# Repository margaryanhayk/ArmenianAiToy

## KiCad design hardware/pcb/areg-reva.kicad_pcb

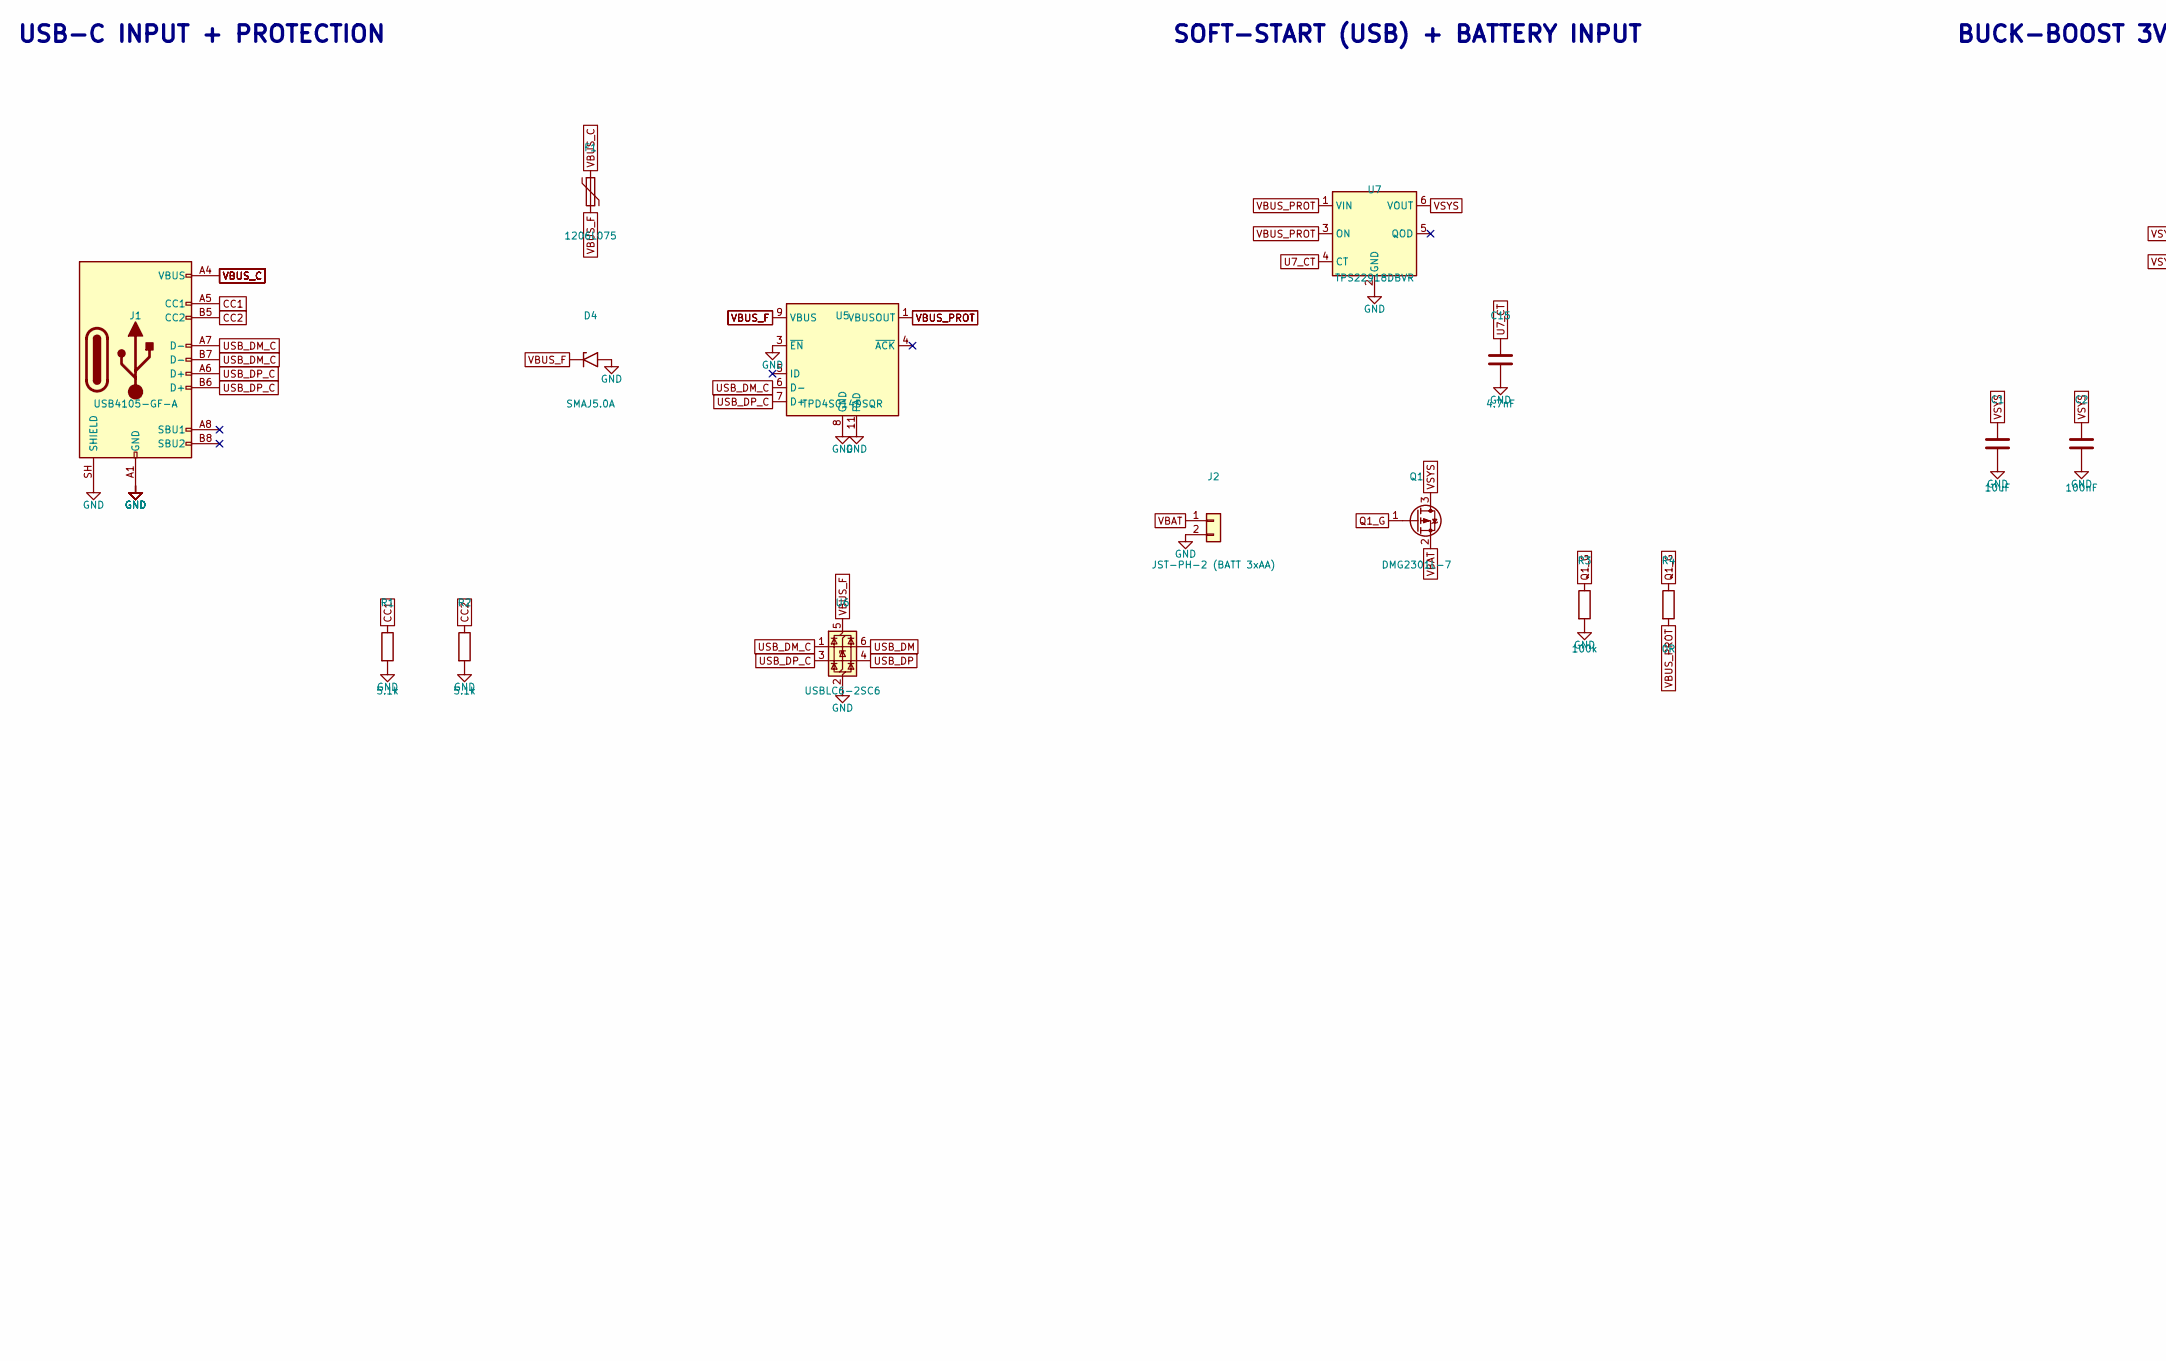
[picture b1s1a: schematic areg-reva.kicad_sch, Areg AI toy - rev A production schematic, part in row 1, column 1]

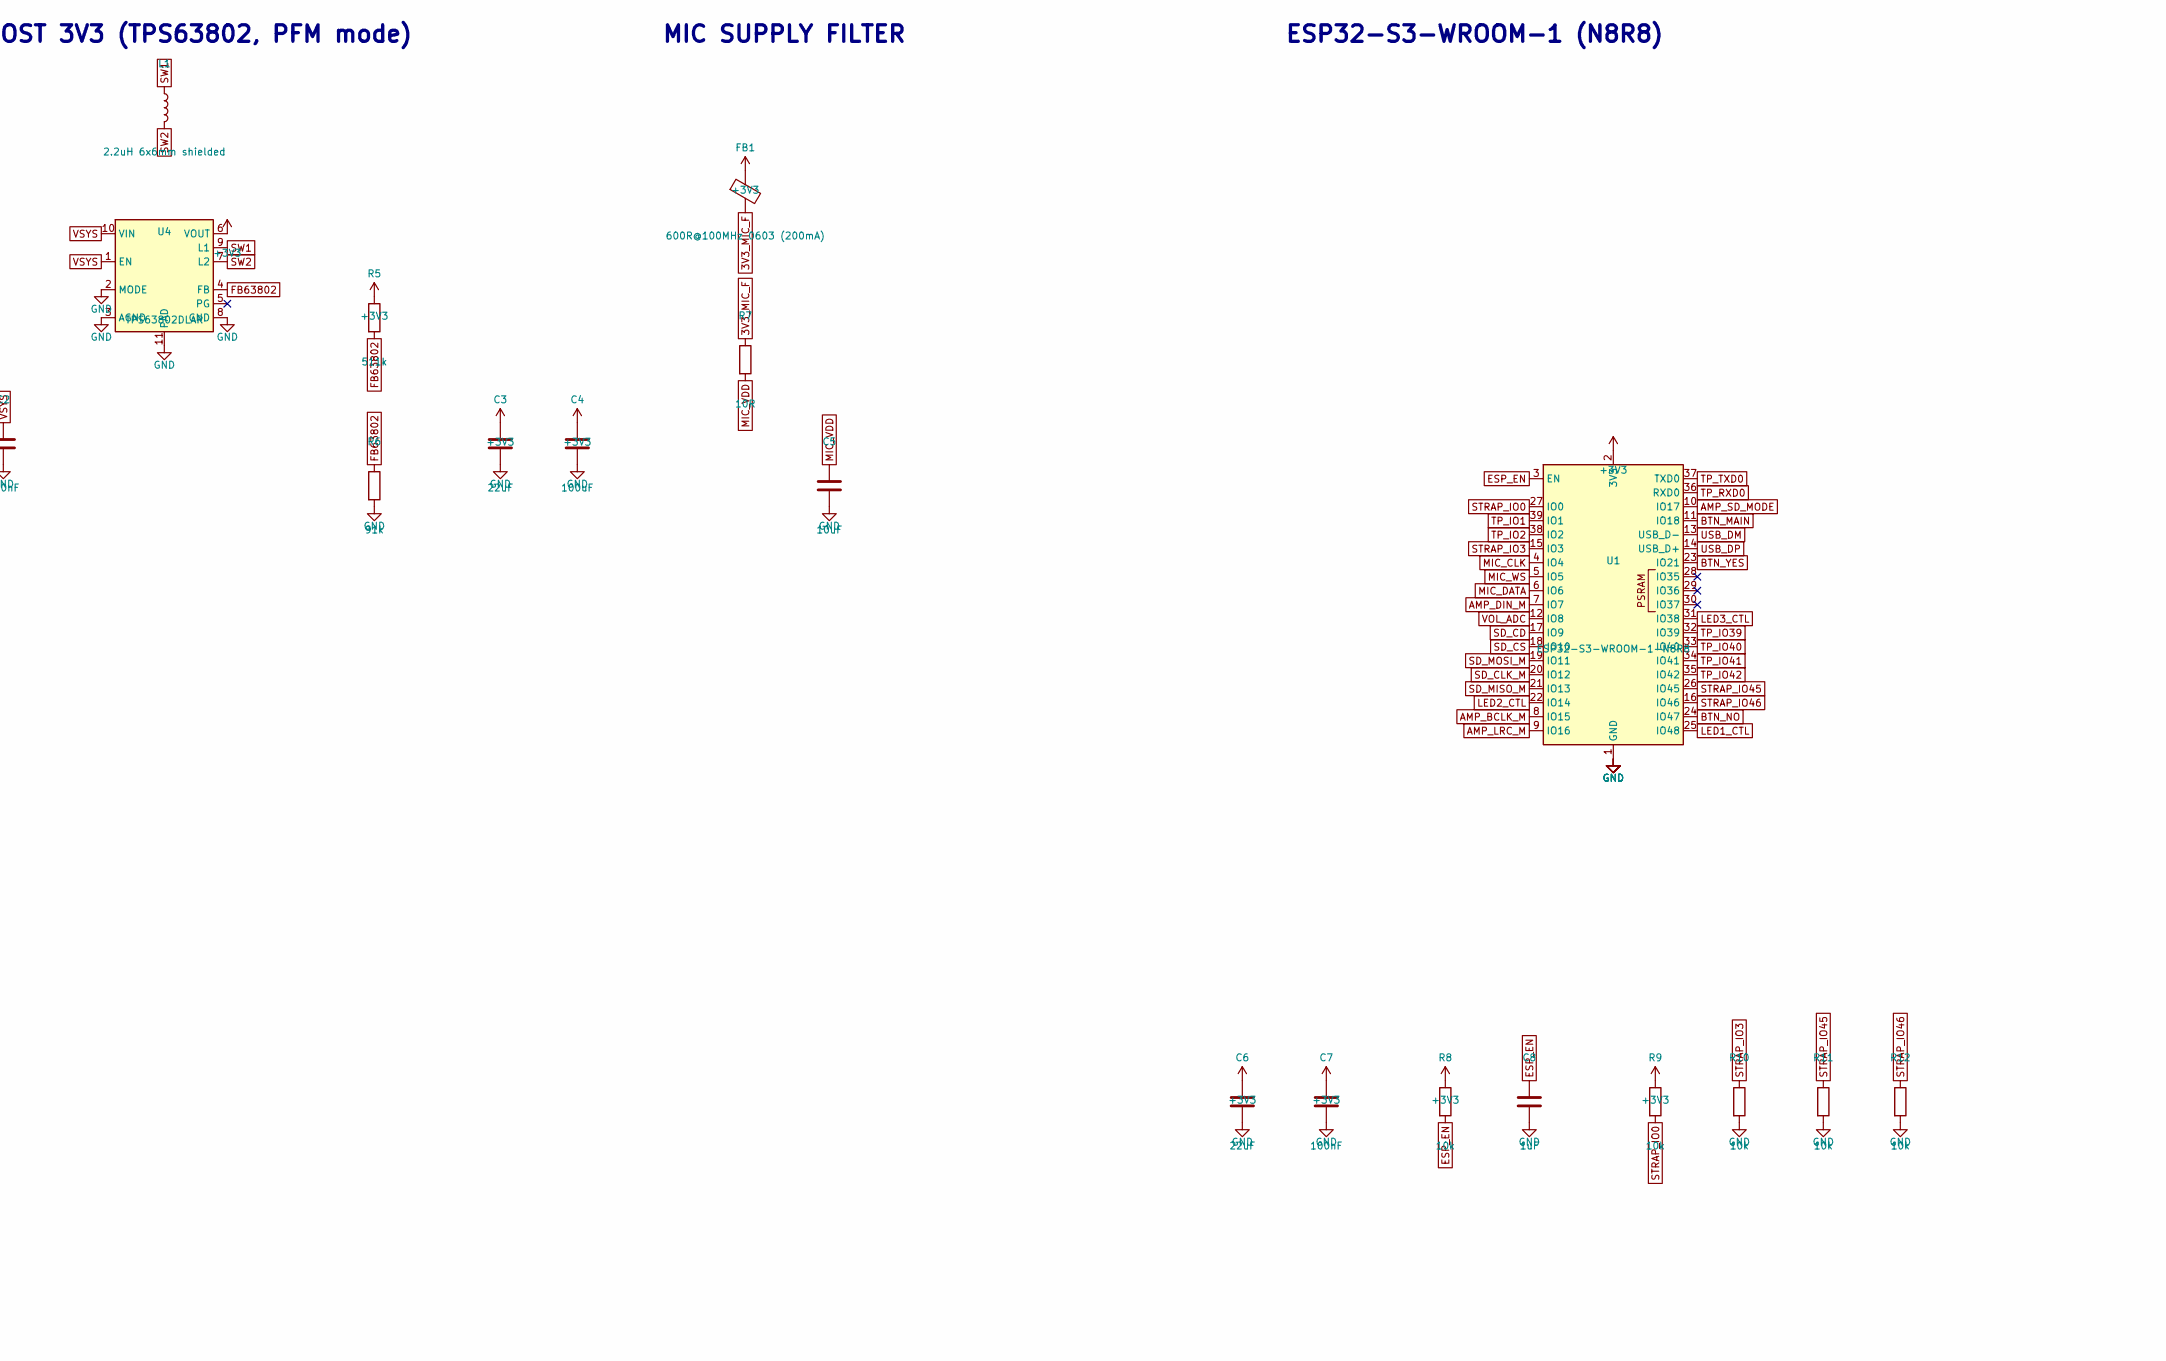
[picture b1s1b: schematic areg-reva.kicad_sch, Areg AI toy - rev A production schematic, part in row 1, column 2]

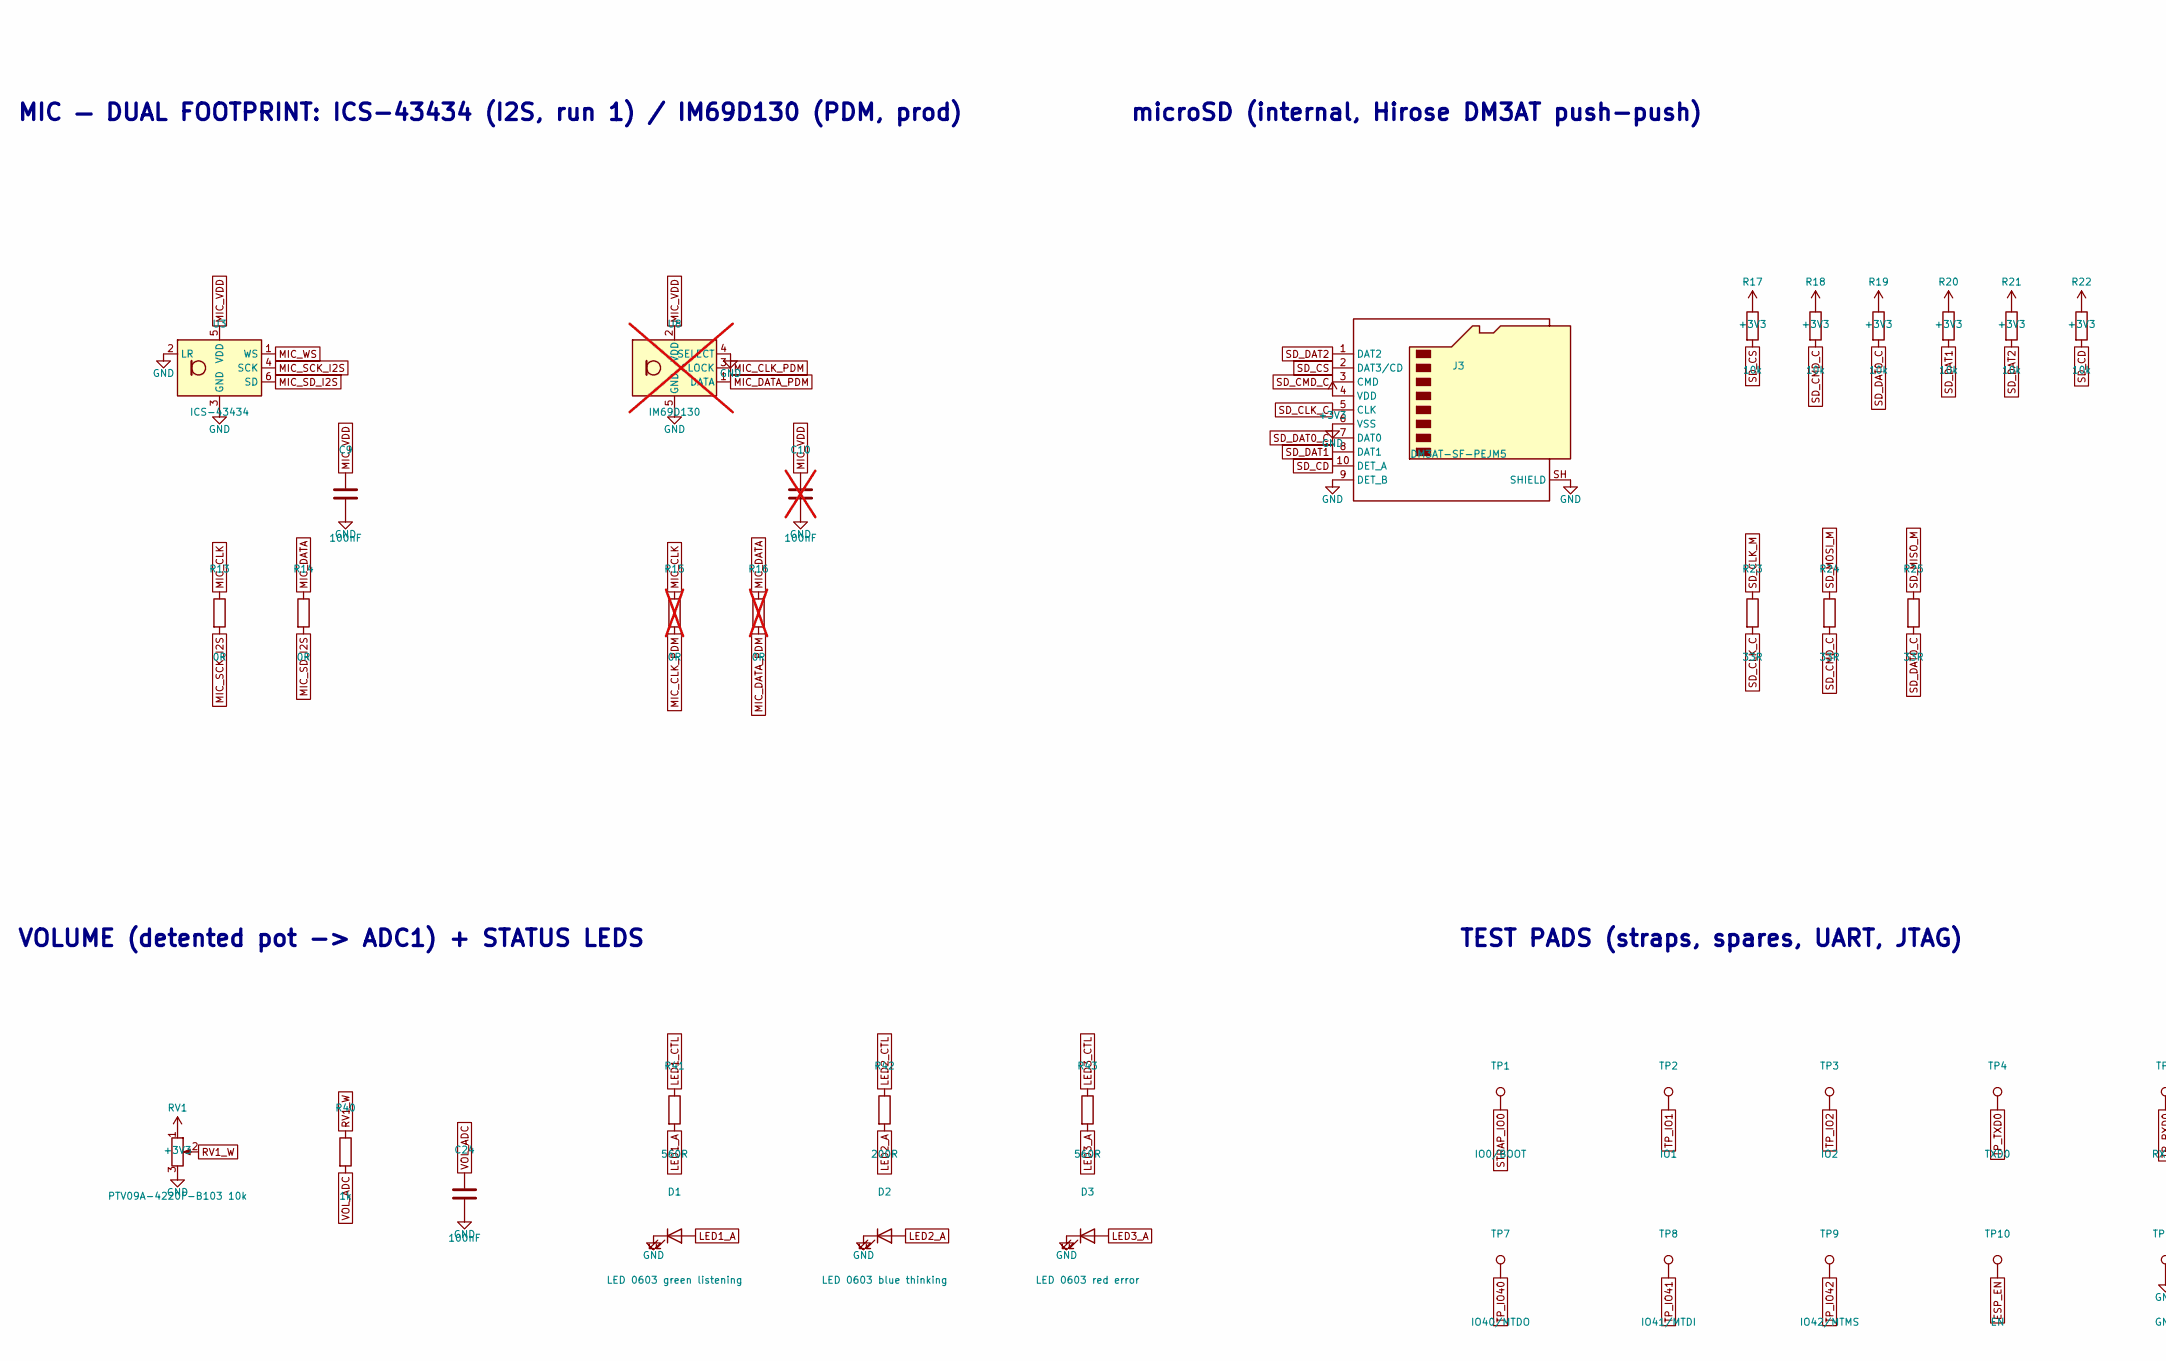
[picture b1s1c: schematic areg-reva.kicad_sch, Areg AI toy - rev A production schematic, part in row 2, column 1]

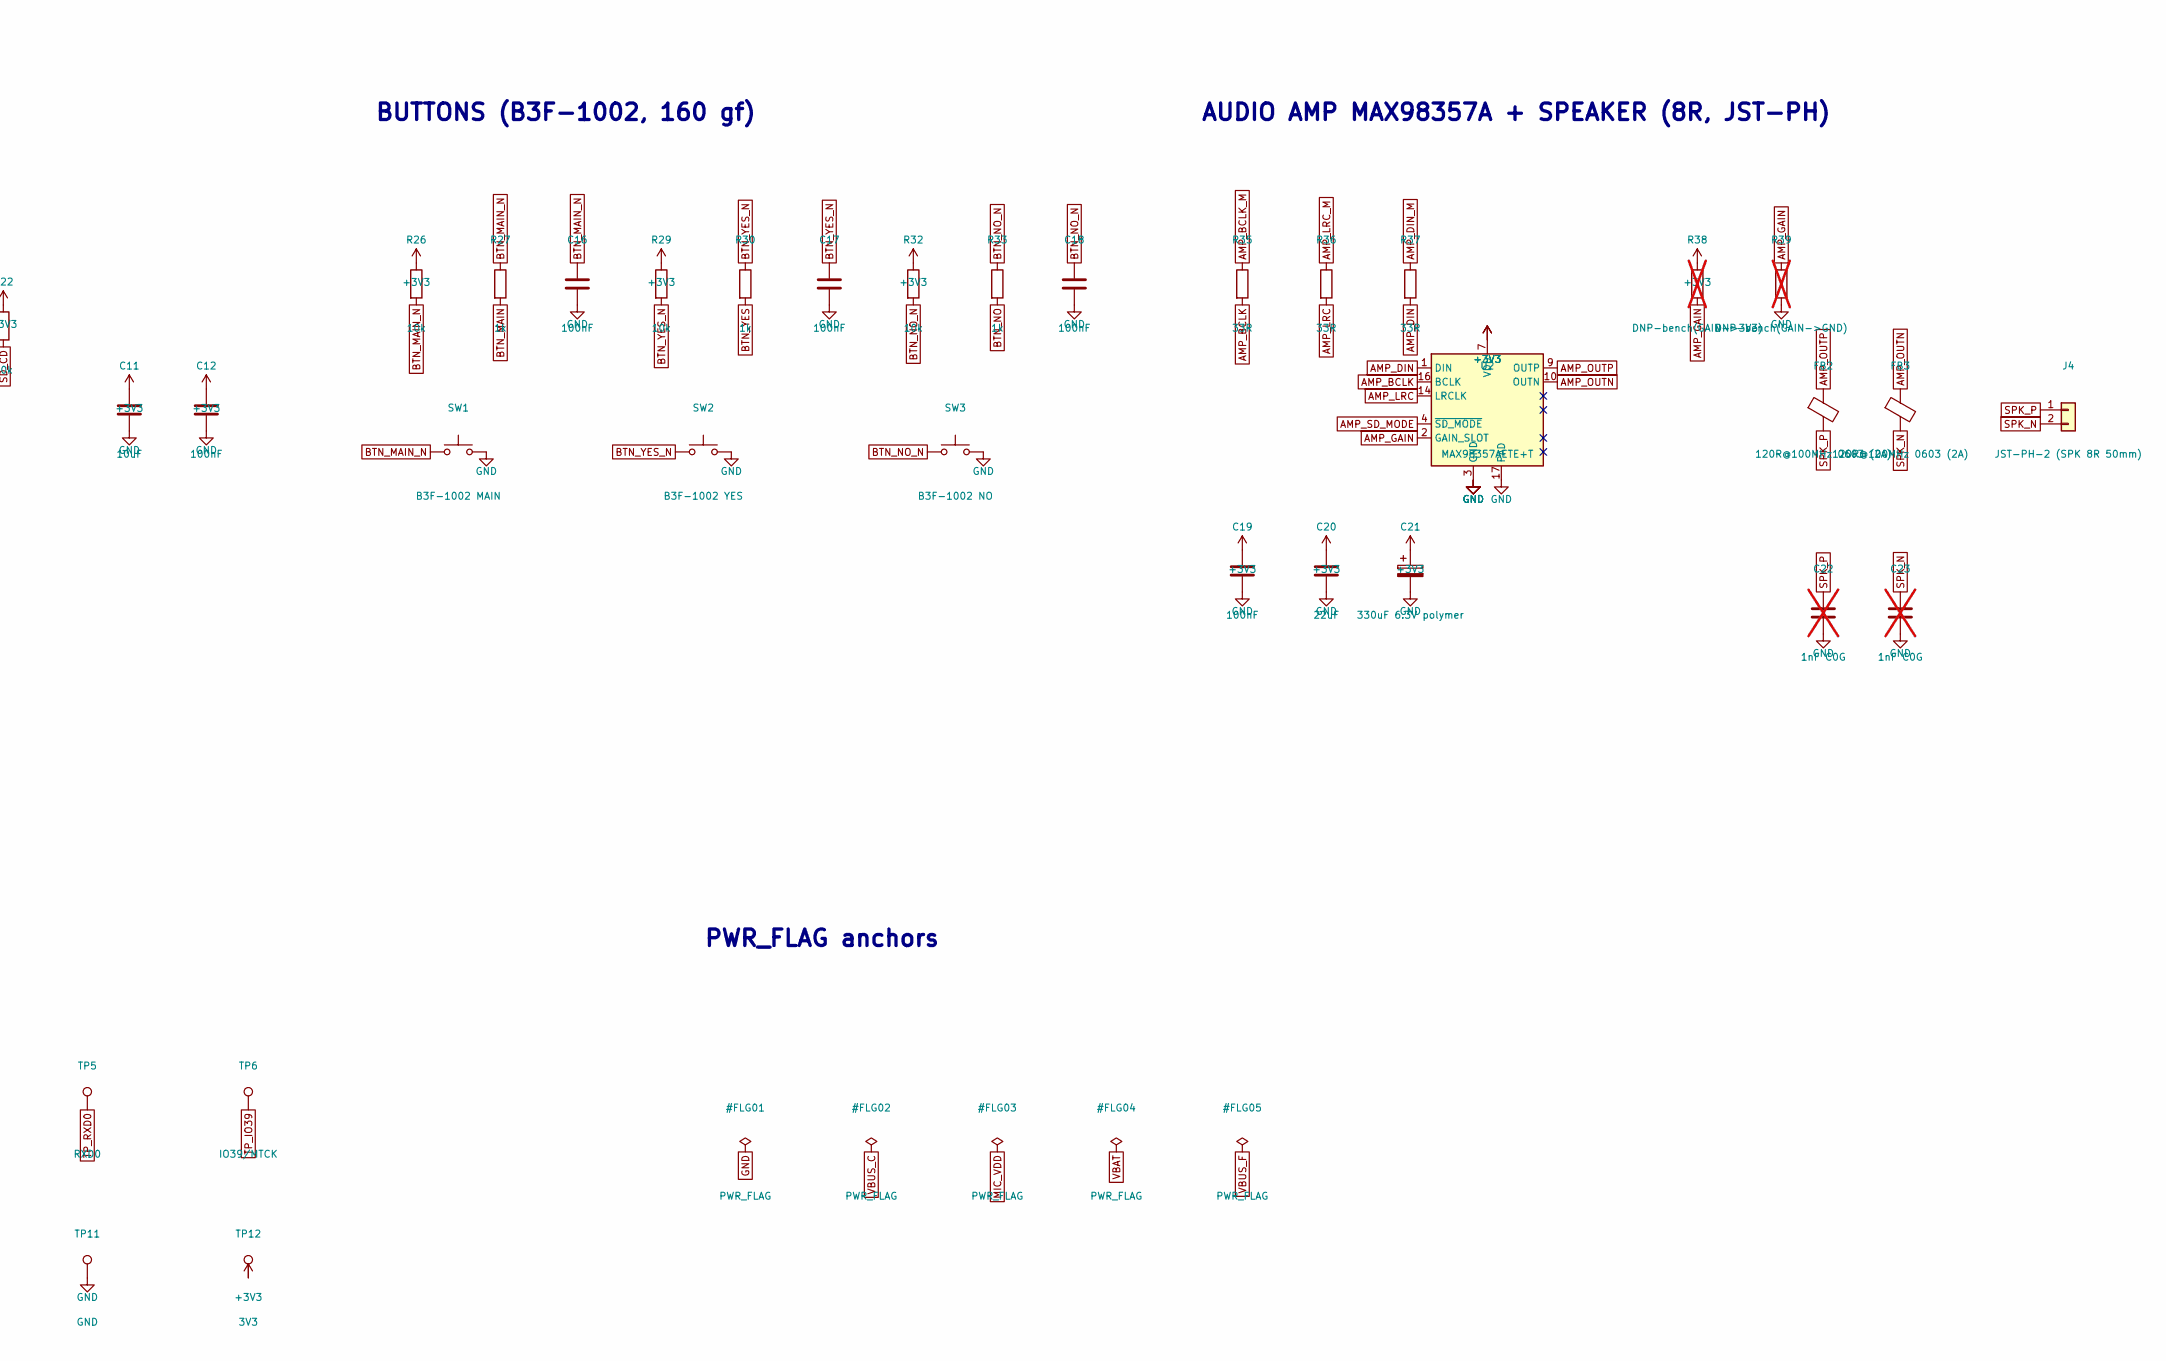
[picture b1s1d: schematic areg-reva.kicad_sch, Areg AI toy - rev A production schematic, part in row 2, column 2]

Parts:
C1, C5, C11: 10uF; C_0603_1608Metric; LCSC C19702
C2, C7, C9, C12, C16, C17, C18, C19, C24: 100nF; C_0402_1005Metric; LCSC C1525
C3, C6, C20: 22uF; C_0603_1608Metric
C4: 100uF; C_1206_3216Metric
C8: 1uF; C_0402_1005Metric; LCSC C52923
C10: 100nF; C_0402_1005Metric; LCSC C1525; not fitted
C15: 4.7nF; C_0402_1005Metric
C21: 330uF 6.3V polymer; CP_EIA-7343-31_Kemet-D; LCSC C79113
C22, C23: 1nF C0G; C_0402_1005Metric; not fitted
D1: LED 0603 green listening; LED_0603_1608Metric
D2: LED 0603 blue thinking; LED_0603_1608Metric
D3: LED 0603 red error; LED_0603_1608Metric
D4: SMAJ5.0A; D_SMA; LCSC C83329
F1: 1206L075; Fuse_1206_3216Metric
FB1: 600R@100MHz 0603 (200mA); L_0603_1608Metric; LCSC C1002
FB2, FB3: 120R@100MHz 0603 (2A); L_0603_1608Metric; LCSC C14709
J1: USB4105-GF-A; USB_C_Receptacle_GCT_USB4105-xx-A_16P_TopMnt_Horizontal
J2: JST-PH-2 (BATT 3xAA); JST_PH_B2B-PH-K_1x02_P2.00mm_Vertical
J3: DM3AT-SF-PEJM5; microSD_HC_Hirose_DM3AT-SF-PEJM5
J4: JST-PH-2 (SPK 8R 50mm); JST_PH_B2B-PH-K_1x02_P2.00mm_Vertical
L1: 2.2uH 6x6mm shielded; L_TDK_VLS6045EX_VLS6045AF; LCSC C2849533
Q1: DMG2301L-7; SOT-23; LCSC C102619
R1, R2: 5.1k; R_0402_1005Metric; LCSC C25905
R3: 100k; R_0402_1005Metric; LCSC C25741
R4, R13, R14: 0R; R_0603_1608Metric
R5: 511k; R_0603_1608Metric
R6: 91k; R_0603_1608Metric
R7: 10R; R_0402_1005Metric
R8, R9, R10, R11, R12, R17, R18, R19, R20, R21, R22, R26, R29, R32: 10k; R_0402_1005Metric; LCSC C25744
R15, R16: 0R; R_0603_1608Metric; not fitted
R23, R24, R25, R35, R36, R37: 33R; R_0603_1608Metric
R27, R30, R33, R40: 1k; R_0402_1005Metric; LCSC C11702
R38: DNP-bench(GAIN->3V3); R_0402_1005Metric; not fitted
R39: DNP-bench(GAIN->GND); R_0402_1005Metric; not fitted
R41, R43: 560R; R_0603_1608Metric
R42: 200R; R_0603_1608Metric
RV1: PTV09A-4220F-B103 10k; Potentiometer_Bourns_PTV09A-1_Single_Vertical
SW1: B3F-1002 MAIN; SW_TH_Tactile_Omron_B3F-100x
SW2: B3F-1002 YES; SW_TH_Tactile_Omron_B3F-100x
SW3: B3F-1002 NO; SW_TH_Tactile_Omron_B3F-100x
TP1: IO0/BOOT; TestPoint_Pad_1.5x1.5mm
TP2: IO1; TestPoint_Pad_1.5x1.5mm
TP3: IO2; TestPoint_Pad_1.5x1.5mm
TP4: TXD0; TestPoint_Pad_1.5x1.5mm
TP5: RXD0; TestPoint_Pad_1.5x1.5mm
TP6: IO39/MTCK; TestPoint_Pad_1.5x1.5mm
TP7: IO40/MTDO; TestPoint_Pad_1.5x1.5mm
TP8: IO41/MTDI; TestPoint_Pad_1.5x1.5mm
TP9: IO42/MTMS; TestPoint_Pad_1.5x1.5mm
TP10: EN; TestPoint_Pad_1.5x1.5mm
TP11: GND; TestPoint_Pad_1.5x1.5mm
TP12: 3V3; TestPoint_Pad_1.5x1.5mm
U1: ESP32-S3-WROOM-1-N8R8; ESP32-S3-WROOM-1
U2: MAX98357AETE+T; TQFN-16-1EP_3x3mm_P0.5mm_EP1.6x1.6mm; LCSC C910544
U3: ICS-43434; InvenSense_ICS-43434-6_3.5x2.65mm
U4: TPS63802DLAR; Texas_S-PVSON-N10
U5: TPD4S014DSQR; Texas_DSQ0010A_WSON-10-1EP_2x2mm_P0.4mm_EP0.9x1.5mm
U6: USBLC6-2SC6; SOT-23-6; LCSC C7519
U7: TPS22918DBVR; SOT-23-6; LCSC C131941
U8: IM69D130; Infineon_PG-LLGA-5-1; not fitted

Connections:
3V3_MIC_F: FB1.2, R7.1
+3V3: C3.1, C4.1, C6.1, C7.1, C11.1, C12.1, C19.1, C20.1, C21.1, FB1.1, J3.4 (VDD), R5.1, R8.1, R9.1, R17.1, R18.1, R19.1, R20.1, R21.1, R22.1, R26.1, R29.1, R32.1, R38.1, RV1.1, TP12.1, U1.2 (3V3), U2.7 (VDD), U2.8 (VDD), U4.6 (VOUT)
AMP_BCLK: R35.2, U2.16 (BCLK)
AMP_BCLK_M: R35.1, U1.8 (IO15)
AMP_DIN: R37.2, U2.1 (DIN)
AMP_DIN_M: R37.1, U1.7 (IO7)
AMP_GAIN: R38.2, R39.1, U2.2 (GAIN_SLOT)
AMP_LRC: R36.2, U2.14 (LRCLK)
AMP_LRC_M: R36.1, U1.9 (IO16)
AMP_OUTN: FB3.1, U2.10 (OUTN)
AMP_OUTP: FB2.1, U2.9 (OUTP)
AMP_SD_MODE: U1.10 (IO17), U2.4 (~SD_MODE)
BTN_MAIN: R27.2, U1.11 (IO18)
BTN_MAIN_N: C16.1, R26.2, R27.1, SW1.1
BTN_NO: R33.2, U1.24 (IO47)
BTN_NO_N: C18.1, R32.2, R33.1, SW3.1
BTN_YES: R30.2, U1.23 (IO21)
BTN_YES_N: C17.1, R29.2, R30.1, SW2.1
CC1: J1.A5 (CC1), R1.1
CC2: J1.B5 (CC2), R2.1
ESP_EN: C8.1, R8.2, TP10.1, U1.3 (EN)
FB63802: R5.2, R6.1, U4.4 (FB)
GND: C1.2, C2.2, C3.2, C4.2, C5.2, C6.2, C7.2, C8.2, C9.2, C10.2, C11.2, C12.2, C15.2, C16.2, C17.2, C18.2, C19.2, C20.2, C21.2, C22.2, C23.2, C24.2, D1.1 (K), D2.1 (K), D3.1 (K), D4.2 (A2), J1.A1 (GND), J1.A12 (GND), J1.B1 (GND), J1.B12 (GND), J1.SH (SHIELD), J2.2, J3.6 (VSS), J3.9 (DET_B), J3.SH (SHIELD), R1.2, R2.2, R3.2, R6.2, R10.2, R11.2, R12.2, R39.2, RV1.3, SW1.2, SW2.2, SW3.2, TP11.1, U1.1 (GND), U1.40 (GND), U1.41 (GND), U2.3 (GND), U2.11 (GND), U2.15 (GND), U2.17 (PAD), U3.2 (LR), U3.3 (GND), U4.2 (MODE), U4.3 (AGND), U4.8 (GND), U4.11 (PAD), U5.3 (~EN), U5.8 (GND), U5.11 (PAD), U6.2 (GND), U7.2 (GND), U8.4 (SELECT), U8.5 (GND)
LED1_A: D1.2 (A), R41.2
LED1_CTL: R41.1, U1.25 (IO48)
LED2_A: D2.2 (A), R42.2
LED2_CTL: R42.1, U1.22 (IO14)
LED3_A: D3.2 (A), R43.2
LED3_CTL: R43.1, U1.31 (IO38)
MIC_CLK: R13.1, R15.1, U1.4 (IO4)
MIC_CLK_PDM: R15.2, U8.3 (CLOCK)
MIC_DATA: R14.1, R16.1, U1.6 (IO6)
MIC_DATA_PDM: R16.2, U8.1 (DATA)
MIC_SCK_I2S: R13.2, U3.4 (SCK)
MIC_SD_I2S: R14.2, U3.6 (SD)
MIC_VDD: C5.1, C9.1, C10.1, R7.2, U3.5 (VDD), U8.2 (VDD)
MIC_WS: U1.5 (IO5), U3.1 (WS)
Q1_G: Q1.1 (G), R3.1, R4.1
RV1_W: R40.1, RV1.2
SD_CD: J3.10 (DET_A), R22.2, U1.17 (IO9)
SD_CLK_C: J3.5 (CLK), R23.2
SD_CLK_M: R23.1, U1.20 (IO12)
SD_CMD_C: J3.3 (CMD), R18.2, R24.2
SD_CS: J3.2 (DAT3/CD), R17.2, U1.18 (IO10)
SD_DAT0_C: J3.7 (DAT0), R19.2, R25.2
SD_DAT1: J3.8 (DAT1), R20.2
SD_DAT2: J3.1 (DAT2), R21.2
SD_MISO_M: R25.1, U1.21 (IO13)
SD_MOSI_M: R24.1, U1.19 (IO11)
SPK_N: C23.1, FB3.2, J4.2
SPK_P: C22.1, FB2.2, J4.1
STRAP_IO0: R9.2, TP1.1, U1.27 (IO0)
STRAP_IO3: R10.1, U1.15 (IO3)
STRAP_IO45: R11.1, U1.26 (IO45)
STRAP_IO46: R12.1, U1.16 (IO46)
SW1: L1.1, U4.9 (L1)
SW2: L1.2, U4.7 (L2)
TP_IO1: TP2.1, U1.39 (IO1)
TP_IO2: TP3.1, U1.38 (IO2)
TP_IO39: TP6.1, U1.32 (IO39)
TP_IO40: TP7.1, U1.33 (IO40)
TP_IO41: TP8.1, U1.34 (IO41)
TP_IO42: TP9.1, U1.35 (IO42)
TP_RXD0: TP5.1, U1.36 (RXD0)
TP_TXD0: TP4.1, U1.37 (TXD0)
U7_CT: C15.1, U7.4 (CT)
USB_DM: U1.13 (USB_D-), U6.6 (I/O1)
USB_DM_C: J1.A7 (D-), J1.B7 (D-), U5.6 (D-), U6.1 (I/O1)
USB_DP: U1.14 (USB_D+), U6.4 (I/O2)
USB_DP_C: J1.A6 (D+), J1.B6 (D+), U5.7 (D+), U6.3 (I/O2)
VBAT: J2.1, Q1.2 (S)
VBUS_C: F1.1, J1.A4 (VBUS), J1.A9 (VBUS), J1.B4 (VBUS), J1.B9 (VBUS)
VBUS_F: D4.1 (A1), F1.2, U5.9 (VBUS), U5.10 (VBUS), U6.5 (VBUS)
VBUS_PROT: R4.2, U5.1 (VBUSOUT), U5.2 (VBUSOUT), U7.1 (VIN), U7.3 (ON)
VOL_ADC: C24.1, R40.2, U1.12 (IO8)
VSYS: C1.1, C2.1, Q1.3 (D), U4.1 (EN), U4.10 (VIN), U7.6 (VOUT)

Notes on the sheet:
USB-C INPUT + PROTECTION
SOFT-START (USB) + BATTERY INPUT
BUCK-BOOST 3V3 (TPS63802, PFM mode)
MIC SUPPLY FILTER
ESP32-S3-WROOM-1 (N8R8)
MIC — DUAL FOOTPRINT: ICS-43434 (I2S, run 1) / IM69D130 (PDM, prod)
microSD (internal, Hirose DM3AT push-push)
BUTTONS (B3F-1002, 160 gf)
AUDIO AMP MAX98357A + SPEAKER (8R, JST-PH)
VOLUME (detented pot -> ADC1) + STATUS LEDS
TEST PADS (straps, spares, UART, JTAG)
PWR_FLAG anchors

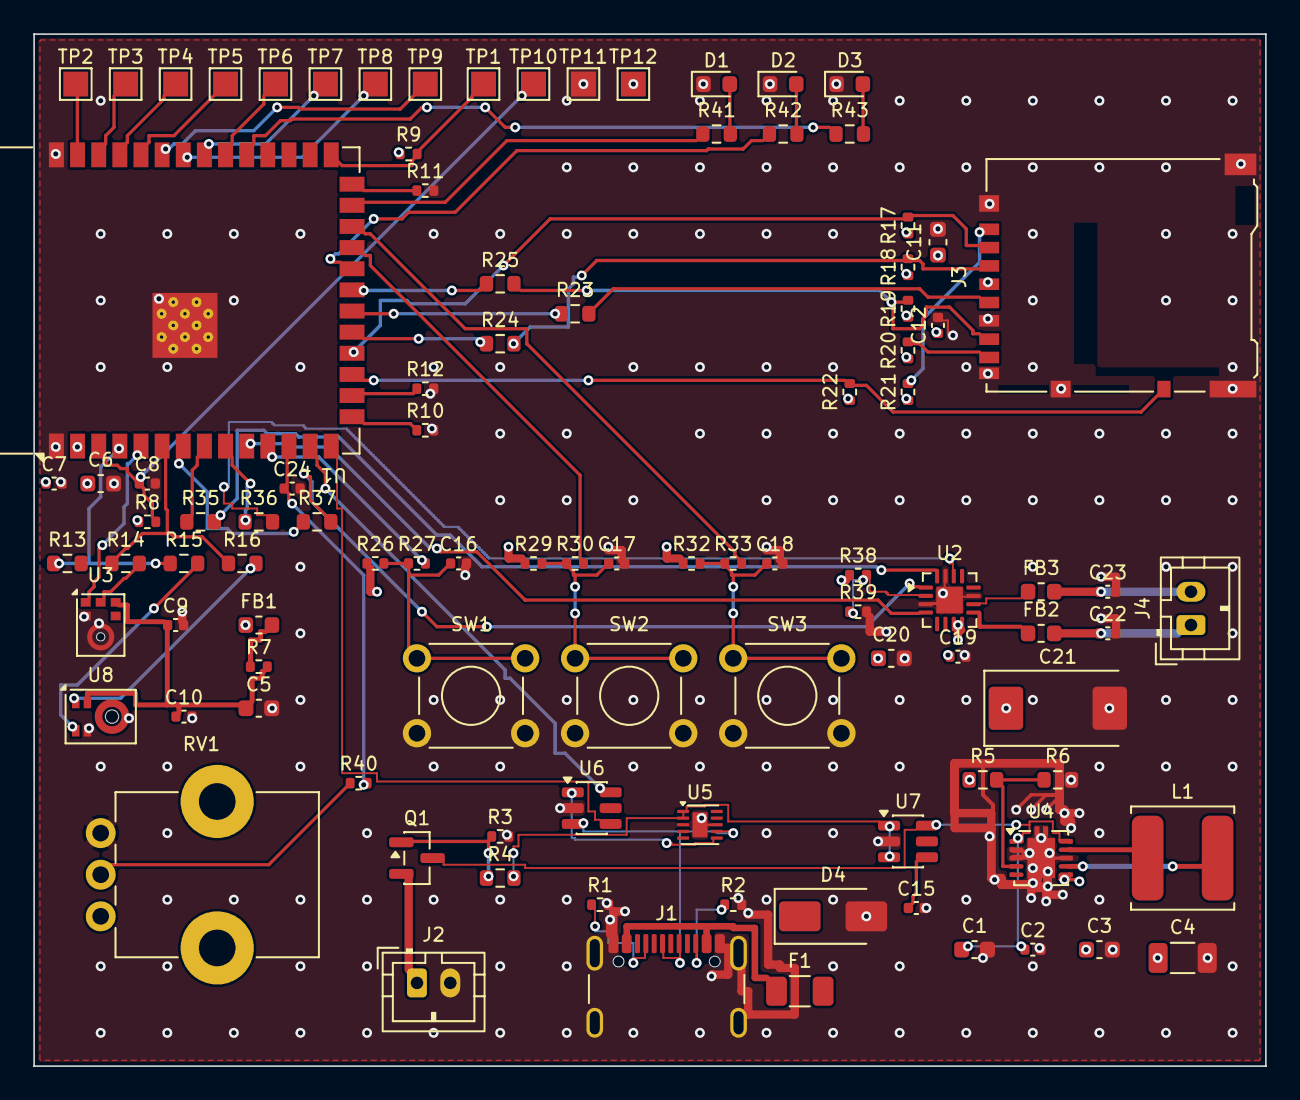
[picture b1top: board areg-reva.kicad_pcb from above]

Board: 4 copper layers, 74.0 x 62.0 mm, 100 parts (0 on the bottom side), 76 nets.
